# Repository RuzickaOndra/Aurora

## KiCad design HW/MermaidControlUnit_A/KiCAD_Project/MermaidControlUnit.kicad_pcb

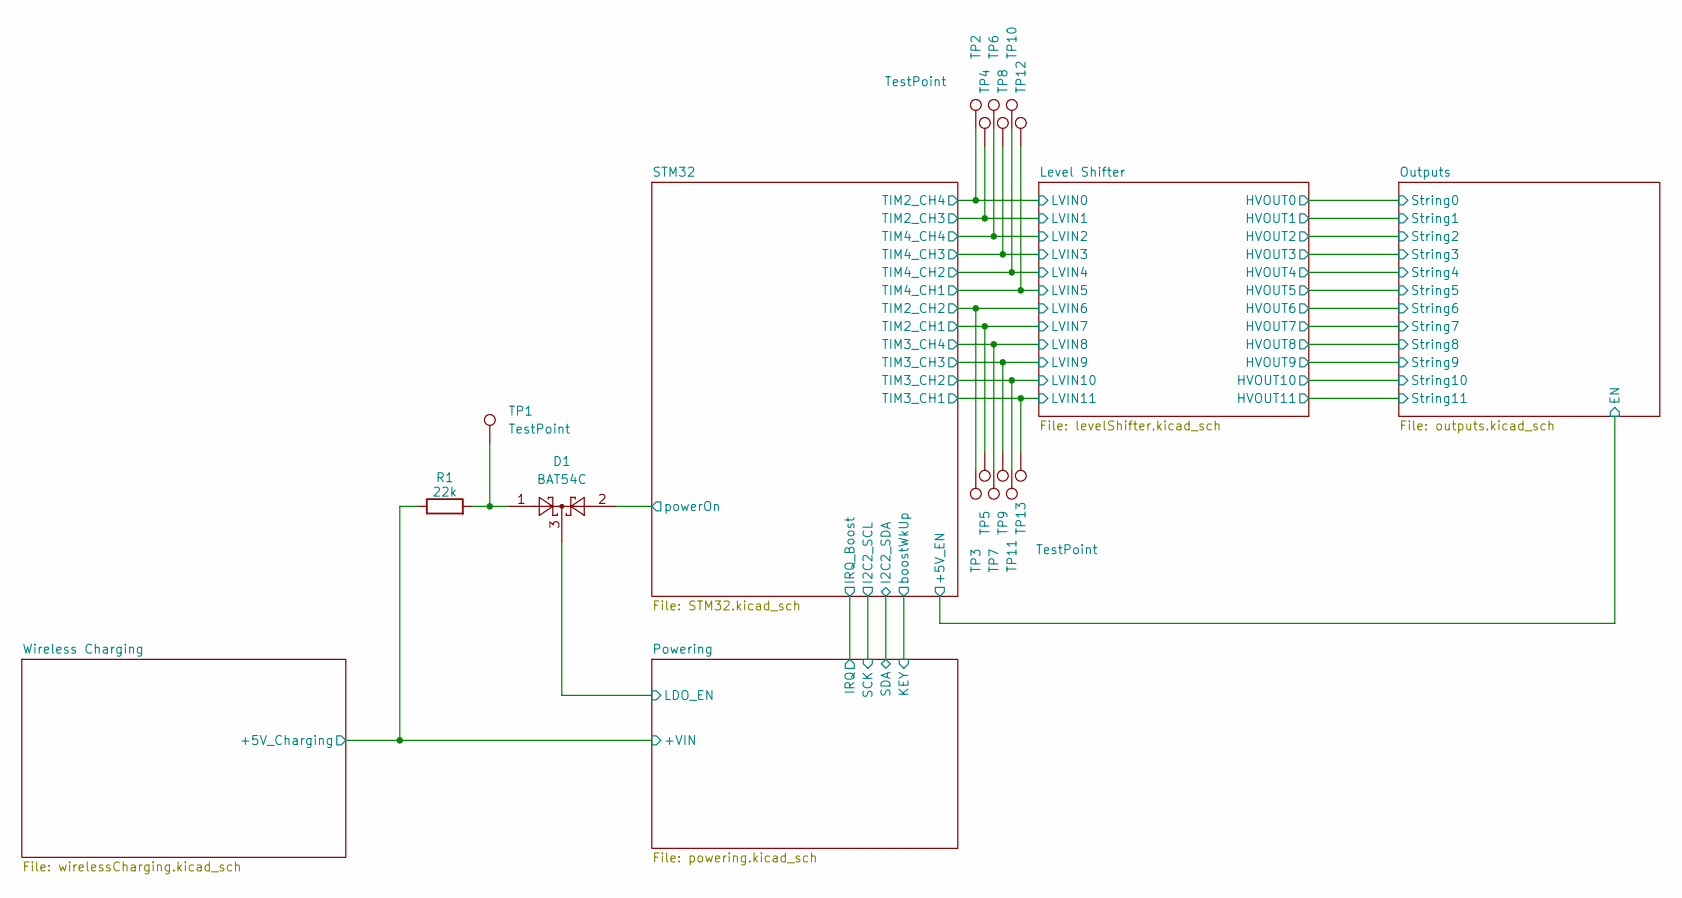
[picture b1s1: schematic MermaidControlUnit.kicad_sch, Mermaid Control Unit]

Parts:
D1: BAT54C; SOT-23; Part Number BAT54CLT1G
R1: 22k; R_0603_1608Metric; Part Number RC0603FR-0722KL
TP1, TP2, TP3, TP4, TP5, TP6, TP7, TP8, TP9, TP10, TP11, TP12, TP13: TestPoint; TestPoint_Pad_D1.5mm

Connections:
/Powering/LDO_EN: D1.3; also elsewhere on the board
/STM32/TIM2_CH1: TP5.1; also elsewhere on the board
/STM32/TIM2_CH2: TP3.1; also elsewhere on the board
/STM32/TIM2_CH3: TP4.1; also elsewhere on the board
/STM32/TIM2_CH4: TP2.1; also elsewhere on the board
/STM32/TIM3_CH1: TP13.1; also elsewhere on the board
/STM32/TIM3_CH2: TP11.1; also elsewhere on the board
/STM32/TIM3_CH3: TP9.1; also elsewhere on the board
/STM32/TIM3_CH4: TP7.1; also elsewhere on the board
/STM32/TIM4_CH1: TP12.1; also elsewhere on the board
/STM32/TIM4_CH2: TP10.1; also elsewhere on the board
/STM32/TIM4_CH3: TP8.1; also elsewhere on the board
/STM32/TIM4_CH4: TP6.1; also elsewhere on the board
/STM32/powerOn: D1.2; also elsewhere on the board
/Wireless Charging/+5V_Charging: R1.1; also elsewhere on the board
unnamed: D1.1, R1.2, TP1.1

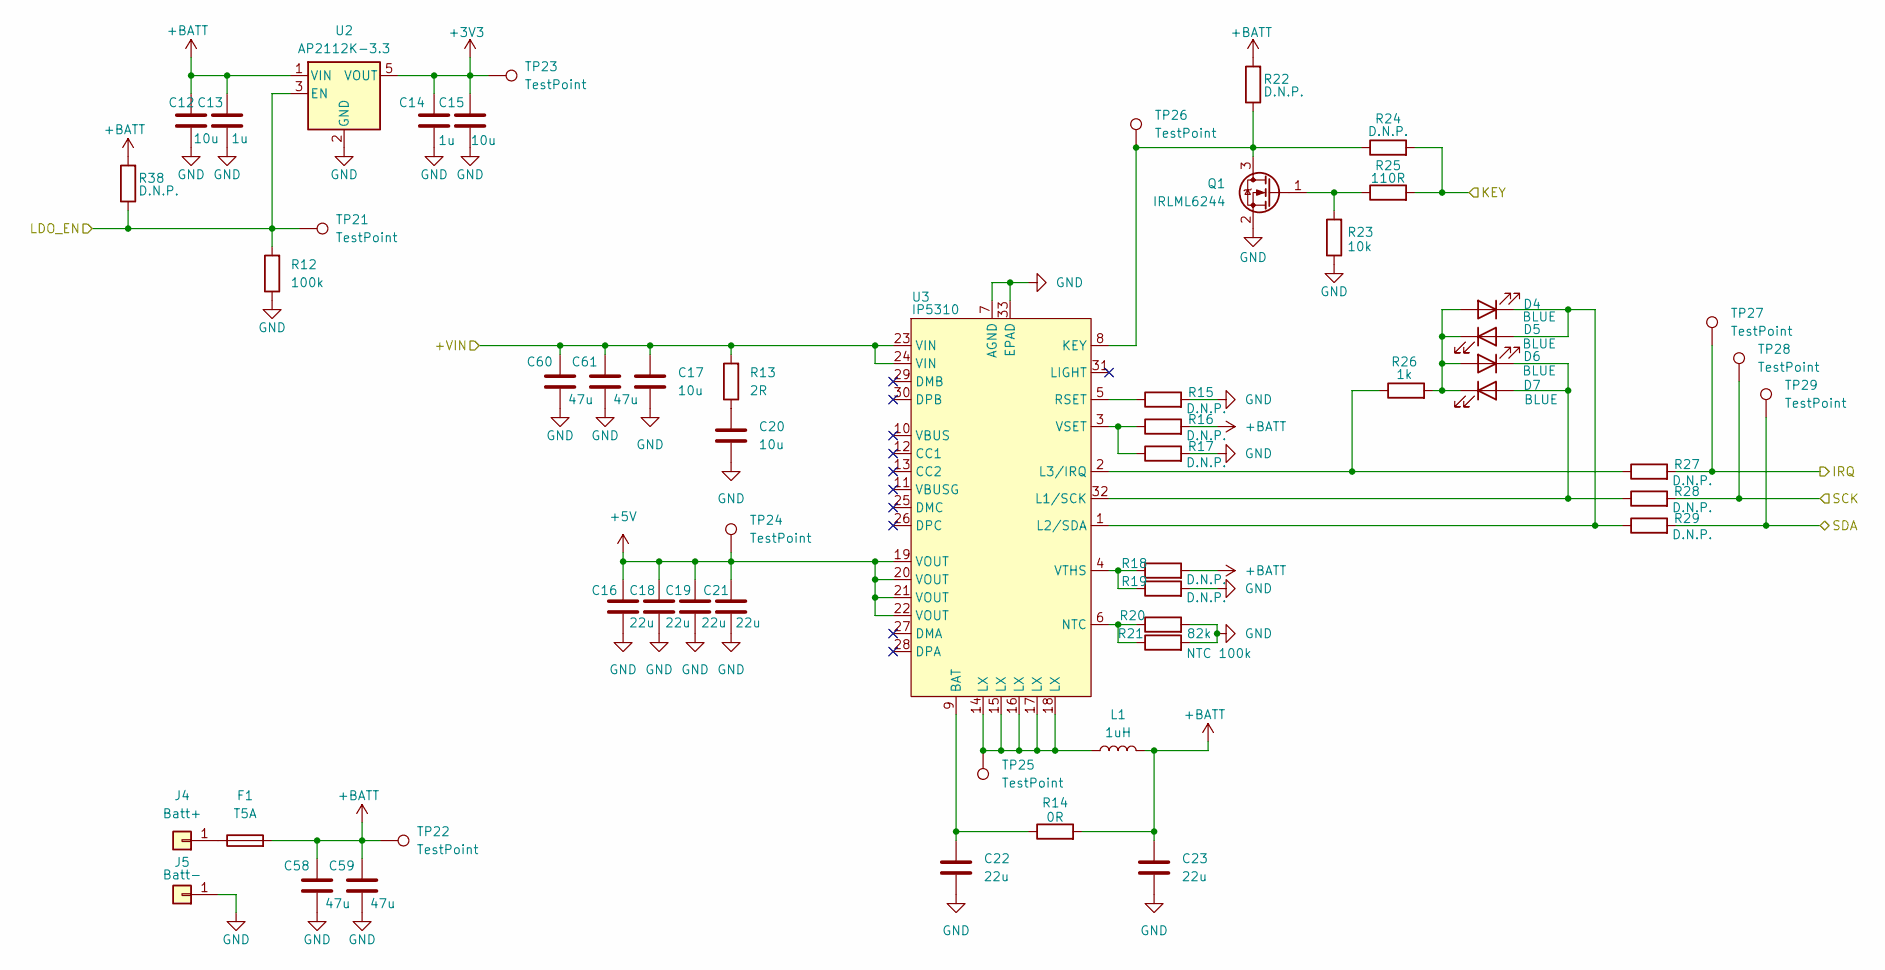
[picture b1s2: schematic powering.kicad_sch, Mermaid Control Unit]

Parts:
C12, C15, C17, C20: 10u; C_0603_1608Metric; Part Number CL10A106MA8NRNC
C13, C14: 1u; C_0603_1608Metric; Part Number CL10A105KB8NNNC
C16, C18, C19, C21, C22, C23: 22u; C_0603_1608Metric; Part Number CL10A226MP8NUNE
C58, C59, C60, C61: 47u; C_0805_2012Metric; Part Number GRM21BR61A476ME15L
D4, D5, D6, D7: BLUE; LED_0603_1608Metric; Part Number APT1608QBC/D
F1: T5A; Fuse_0603_1608Metric; Part Number F0603HI8000V032TM
J4: Batt+; TestPoint_THTPad_2.0x2.0mm_Drill1.0mm
J5: Batt-; TestPoint_THTPad_2.0x2.0mm_Drill1.0mm
L1: 1uH; L_PCC-M1040M-LP; Part Number ETQP4M1R0KVC
Q1: IRLML6244; SOT-23; Part Number IRLML6244TRPBF
R12: 100k; R_0603_1608Metric; Part Number RC0603FR-07100KL
R13: 2R; R_0603_1608Metric; Part Number FRC0603F2R00TS
R14: 0R; R_0603_1608Metric; Part Number RC0603FR-070RL
R15, R16, R17, R18, R19, R22, R24, R27, R28, R29, R38: D.N.P.; R_0603_1608Metric
R20: 82k; R_0603_1608Metric; Part Number RC0603FR-0782KL
R21: NTC 100k; R_0603_1608Metric; Part Number NCU18WF104F6SRB
R23: 10k; R_0603_1608Metric; Part Number RC0603FR-0710KL
R25: 110R; R_0603_1608Metric; Part Number 0603WAF1100T5E
R26: 1k; R_0603_1608Metric; Part Number RC0603FR-071KL
TP21, TP22, TP23, TP24, TP25, TP26, TP27, TP28, TP29: TestPoint; TestPoint_Pad_D1.5mm
U2: AP2112K-3.3; SOT-23-5; Part Number AP2112K-3.3TRG1
U3: IP5310; QFN-32-1EP_5x5mm_P0.5mm_EP3.6x3.6mm_ThermalVias; Part Number IP5310

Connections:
+3V3: C14.1, C15.1, TP23.1, U2.5 (VOUT); also elsewhere on the board
+5V: C16.1, C18.1, C19.1, C21.1, TP24.1, U3.19 (VOUT), U3.20 (VOUT), U3.21 (VOUT), U3.22 (VOUT); also elsewhere on the board
+BATT: C12.1, C13.1, C23.1, C58.1, C59.1, F1.2, L1.2, R14.2, R16.2, R18.2, R22.2, R38.2, TP22.1, U2.1 (VIN); also elsewhere on the board
/Powering/LDO_EN: R12.2, R38.1, TP21.1, U2.3 (EN); also elsewhere on the board
/STM32/I2C2_SCL: R28.2, TP28.1; also elsewhere on the board
/STM32/I2C2_SDA: R29.2, TP29.1; also elsewhere on the board
/STM32/IRQ_Boost: R27.2, TP27.1; also elsewhere on the board
/STM32/boostWkUp: R24.2, R25.2; also elsewhere on the board
/Wireless Charging/+5V_Charging: C17.1, C60.1, C61.1, R13.2, U3.23 (VIN), U3.24 (VIN); also elsewhere on the board
GND: C12.2, C13.2, C14.2, C15.2, C16.2, C17.2, C18.2, C19.2, C20.2, C21.2, C22.2, C23.2, C58.2, C59.2, C60.2, C61.2, J5.1, Q1.2 (S), R12.1, R15.2, R17.2, R19.2, R20.2, R21.2, R23.1, U2.2 (GND), U3.7 (AGND), U3.33 (EPAD); also elsewhere on the board
unnamed: C20.1, R13.1
unnamed: D4.2 (A), D5.1 (K), D6.2 (A), D7.1 (K), R26.2
unnamed: D4.1 (K), D5.2 (A), R29.1, U3.1 (L2/SDA)
unnamed: D6.1 (K), D7.2 (A), R28.1, U3.32 (L1/SCK)
unnamed: F1.1, J4.1
unnamed: L1.1, TP25.1, U3.14 (LX), U3.15 (LX), U3.16 (LX), U3.17 (LX), U3.18 (LX)
unnamed: Q1.3 (D), R22.1, R24.1, TP26.1, U3.8 (KEY)
unnamed: Q1.1 (G), R23.2, R25.1
unnamed: C22.1, R14.1, U3.9 (BAT)
unnamed: R26.1, R27.1, U3.2 (L3/IRQ)
unnamed: R20.1, R21.1, U3.6 (NTC)
unnamed: R15.1, U3.5 (RSET)
unnamed: R16.1, R17.1, U3.3 (VSET)
unnamed: R18.1, R19.1, U3.4 (VTHS)

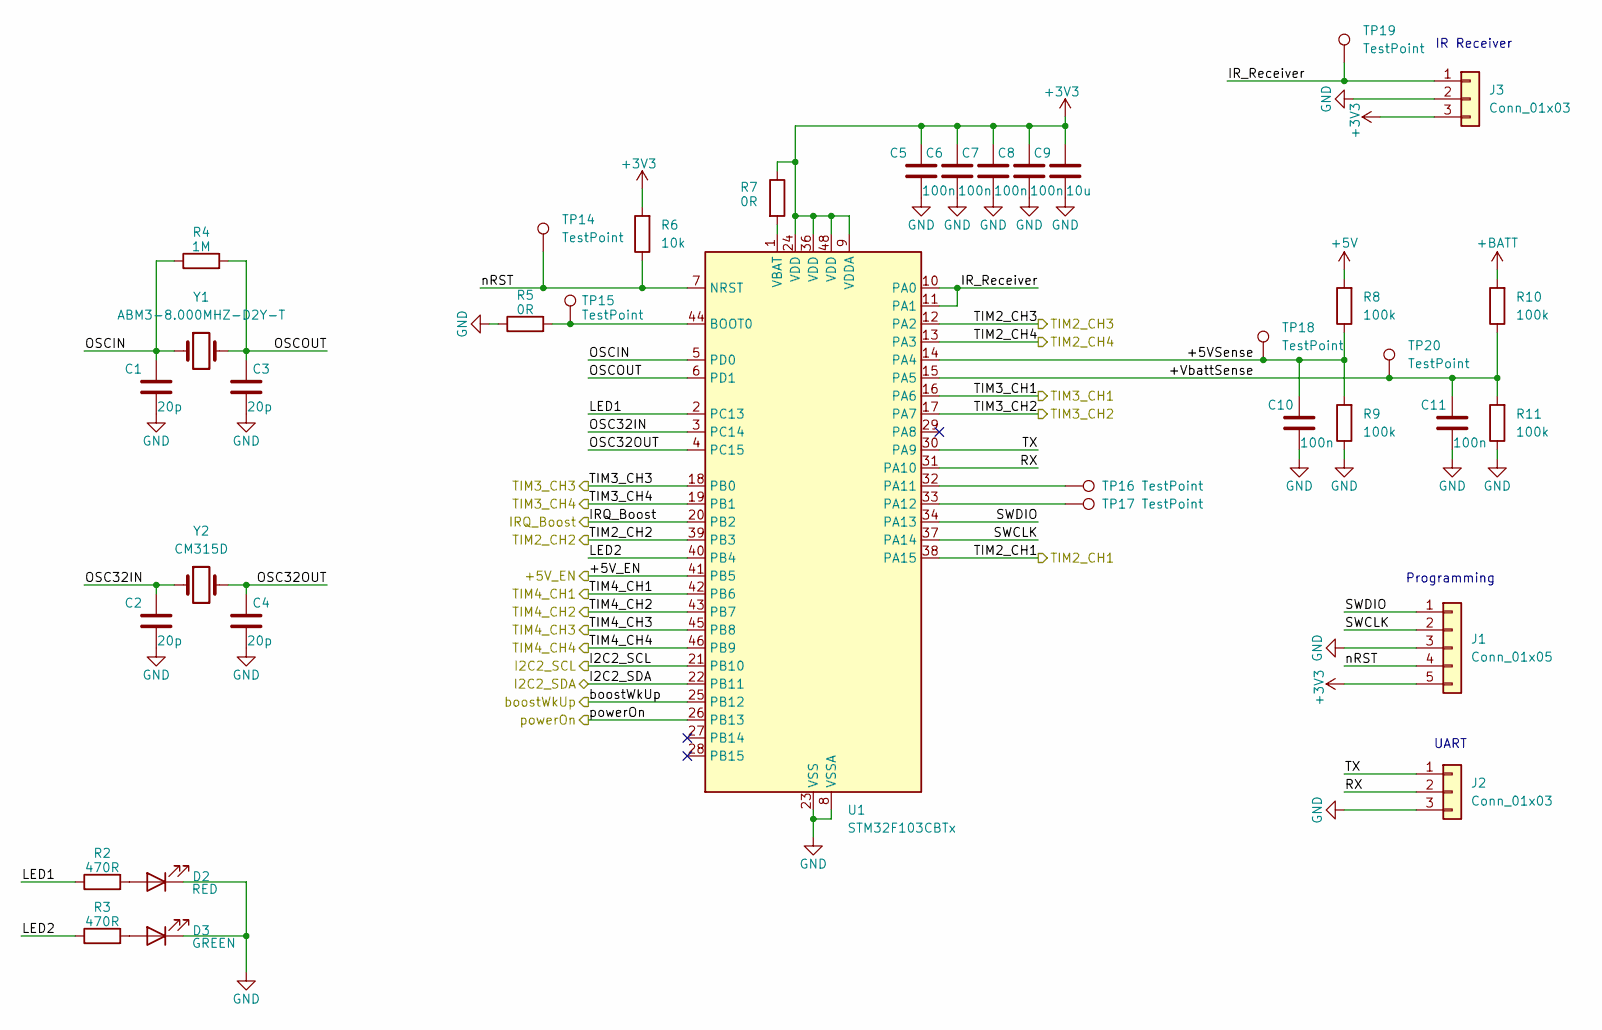
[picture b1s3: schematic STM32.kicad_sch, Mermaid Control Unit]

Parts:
C1, C2, C3, C4: 20p; C_0603_1608Metric; Part Number GCM1885C1H200JA16D
C5, C6, C7, C8, C10, C11: 100n; C_0603_1608Metric; Part Number CC0603KRX7R9BB104
C9: 10u; C_0603_1608Metric; Part Number CL10A106MA8NRNC
D2: RED; LED_0603_1608Metric; Part Number APT1608EC
D3: GREEN; LED_0603_1608Metric; Part Number APT1608CGCK
J1: Conn_01x05; PinHeader_1x05_P2.54mm_Horizontal_SmallSilk; Part Number 5AMW4-10560-105-W0
J2, J3: Conn_01x03; PinHeader_1x03_P2.54mm_Horizontal_SmallSilk; Part Number X6511WR-03H-C60D30R2
R2, R3: 470R; R_0603_1608Metric; Part Number RC0603FR-07470RL
R4: 1M; R_0603_1608Metric; Part Number RC0603FR-071ML
R5, R7: 0R; R_0603_1608Metric; Part Number RC0603FR-070RL
R6: 10k; R_0603_1608Metric; Part Number RC0603FR-0710KL
R8, R9, R10, R11: 100k; R_0603_1608Metric; Part Number RC0603FR-07100KL
TP14, TP15, TP16, TP17, TP18, TP19, TP20: TestPoint; TestPoint_Pad_D1.5mm
U1: STM32F103CBTx; LQFP-48_7x7mm_P0.5mm
Y1: ABM3-8.000MHZ-D2Y-T; Crystal_SMD_Abracon_ABM3-2Pin_5.0x3.2mm; Part Number ABM3-8.000MHZ-D2Y-T
Y2: CM315D; Crystal_SMD_3215-2Pin_3.2x1.5mm; Part Number CM315D32768DZFT

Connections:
+3V3: C5.1, C6.1, C7.1, C8.1, C9.1, J1.5, J3.3, R6.2, R7.1, U1.9 (VDDA), U1.24 (VDD), U1.36 (VDD), U1.48 (VDD); also elsewhere on the board
+5V: R8.2; also elsewhere on the board
+BATT: R10.2; also elsewhere on the board
/STM32/+5VSense: C10.1, R8.1, R9.2, TP18.1, U1.14 (PA4)
/STM32/+5V_EN: U1.41 (PB5); also elsewhere on the board
/STM32/+VbattSense: C11.1, R10.1, R11.2, TP20.1, U1.15 (PA5)
/STM32/I2C2_SCL: U1.21 (PB10); also elsewhere on the board
/STM32/I2C2_SDA: U1.22 (PB11); also elsewhere on the board
/STM32/IRQ_Boost: U1.20 (PB2); also elsewhere on the board
/STM32/IR_Receiver: J3.1, TP19.1, U1.10 (PA0), U1.11 (PA1)
/STM32/LED1: R2.1, U1.2 (PC13)
/STM32/LED2: R3.1, U1.40 (PB4)
/STM32/OSC32IN: C2.1, U1.3 (PC14), Y2.1
/STM32/OSC32OUT: C4.1, U1.4 (PC15), Y2.2
/STM32/OSCIN: C1.1, R4.1, U1.5 (PD0), Y1.1
/STM32/OSCOUT: C3.1, R4.2, U1.6 (PD1), Y1.2
/STM32/RX: J2.2, U1.31 (PA10)
/STM32/SWCLK: J1.2, U1.37 (PA14)
/STM32/SWDIO: J1.1, U1.34 (PA13)
/STM32/TIM2_CH1: U1.38 (PA15); also elsewhere on the board
/STM32/TIM2_CH2: U1.39 (PB3); also elsewhere on the board
/STM32/TIM2_CH3: U1.12 (PA2); also elsewhere on the board
/STM32/TIM2_CH4: U1.13 (PA3); also elsewhere on the board
/STM32/TIM3_CH1: U1.16 (PA6); also elsewhere on the board
/STM32/TIM3_CH2: U1.17 (PA7); also elsewhere on the board
/STM32/TIM3_CH3: U1.18 (PB0); also elsewhere on the board
/STM32/TIM3_CH4: U1.19 (PB1); also elsewhere on the board
/STM32/TIM4_CH1: U1.42 (PB6); also elsewhere on the board
/STM32/TIM4_CH2: U1.43 (PB7); also elsewhere on the board
/STM32/TIM4_CH3: U1.45 (PB8); also elsewhere on the board
/STM32/TIM4_CH4: U1.46 (PB9); also elsewhere on the board
/STM32/TX: J2.1, U1.30 (PA9)
/STM32/boostWkUp: U1.25 (PB12); also elsewhere on the board
/STM32/nRST: J1.4, R6.1, TP14.1, U1.7 (NRST)
/STM32/powerOn: U1.26 (PB13); also elsewhere on the board
GND: C1.2, C2.2, C3.2, C4.2, C5.2, C6.2, C7.2, C8.2, C9.2, C10.2, C11.2, D2.1 (K), D3.1 (K), J1.3, J2.3, J3.2, R5.1, R9.1, R11.1, U1.8 (VSSA), U1.23 (VSS), U1.35 (VSS), U1.47 (VSS); also elsewhere on the board
unnamed: D2.2 (A), R2.2
unnamed: D3.2 (A), R3.2
unnamed: R5.2, TP15.1, U1.44 (BOOT0)
unnamed: TP16.1, U1.32 (PA11)
unnamed: TP17.1, U1.33 (PA12)
unnamed: R7.2, U1.1 (VBAT)

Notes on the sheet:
Programming
UART
IR Receiver

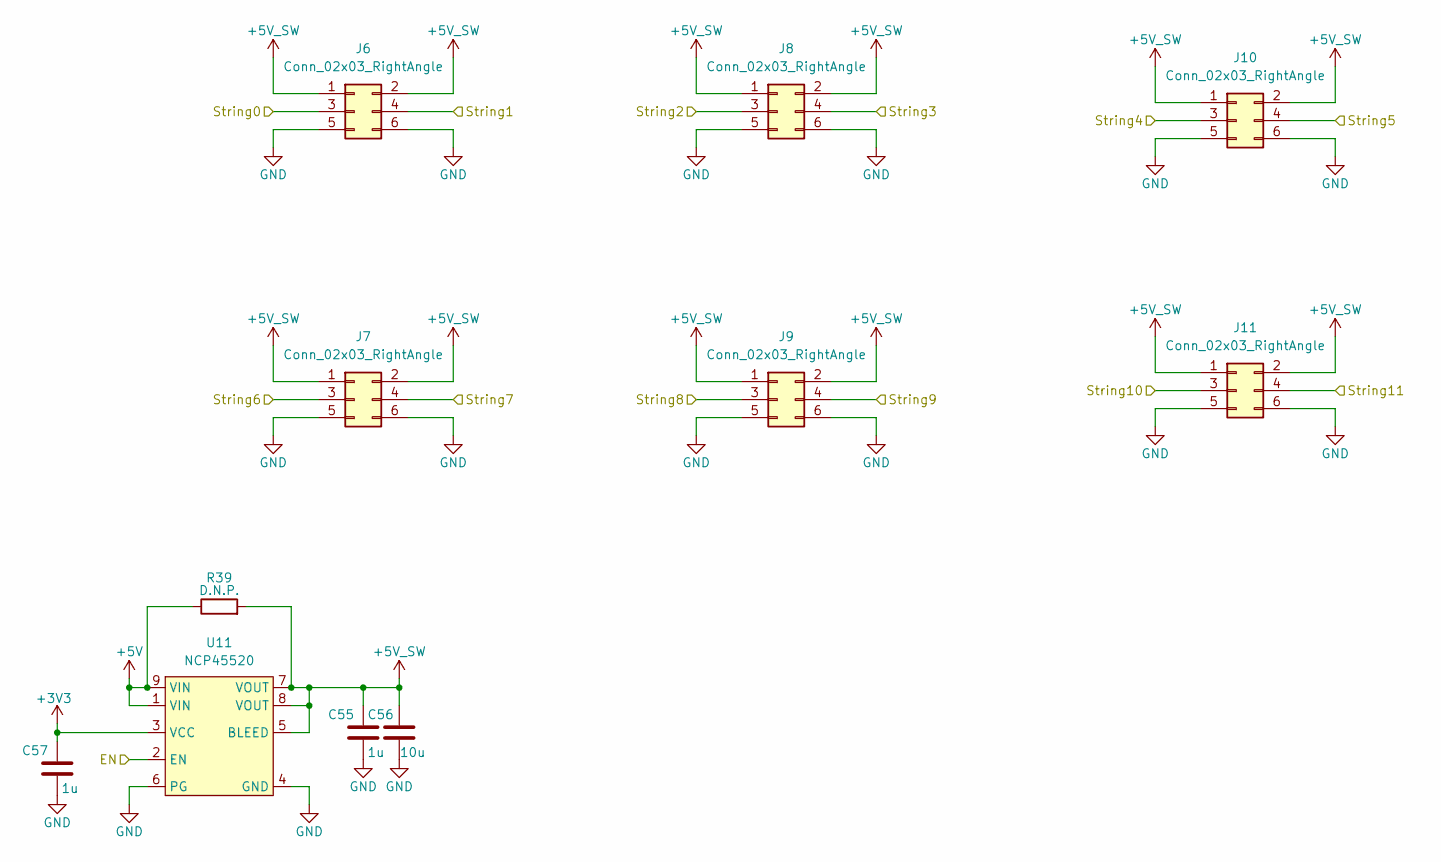
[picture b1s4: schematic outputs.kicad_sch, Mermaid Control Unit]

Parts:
C55, C57: 1u; C_0603_1608Metric; Part Number CL10A105KB8NNNC
C56: 10u; C_0603_1608Metric; Part Number CL10A106MA8NRNC
J6, J7, J8, J9, J10, J11: Conn_02x03_RightAngle; PinHeader_2x03_P2.54mm_Horizontal_SmallSilk; Part Number BX-PZ2.54-2-3PWZ
R39: D.N.P.; R_0603_1608Metric
U11: NCP45520; DFN-8-1EP_2x2mm_P0.5mm_EP1.05x1.75mm; Part Number NCP45520IMNTWG-H

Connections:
+3V3: C57.1, U11.3 (VCC); also elsewhere on the board
+5V: R39.1, U11.1 (VIN), U11.9 (VIN); also elsewhere on the board
+5V_SW: C55.1, C56.1, J6.1, J6.2, J7.1, J7.2, J8.1, J8.2, J9.1, J9.2, J10.1, J10.2, J11.1, J11.2, R39.2, U11.5 (BLEED), U11.7 (VOUT), U11.8 (VOUT)
/Level Shifter/HVOUT0: J6.3; also elsewhere on the board
/Level Shifter/HVOUT1: J6.4; also elsewhere on the board
/Level Shifter/HVOUT2: J8.3; also elsewhere on the board
/Level Shifter/HVOUT3: J8.4; also elsewhere on the board
/Level Shifter/HVOUT4: J10.3; also elsewhere on the board
/Level Shifter/HVOUT5: J10.4; also elsewhere on the board
/Level Shifter/HVOUT6: J7.3; also elsewhere on the board
/Level Shifter/HVOUT7: J7.4; also elsewhere on the board
/Level Shifter/HVOUT8: J9.3; also elsewhere on the board
/Level Shifter/HVOUT9: J9.4; also elsewhere on the board
/Level Shifter/HVOUT10: J11.3; also elsewhere on the board
/Level Shifter/HVOUT11: J11.4; also elsewhere on the board
/STM32/+5V_EN: U11.2 (EN); also elsewhere on the board
GND: C55.2, C56.2, C57.2, J6.5, J6.6, J7.5, J7.6, J8.5, J8.6, J9.5, J9.6, J10.5, J10.6, J11.5, J11.6, U11.4 (GND), U11.6 (PG); also elsewhere on the board

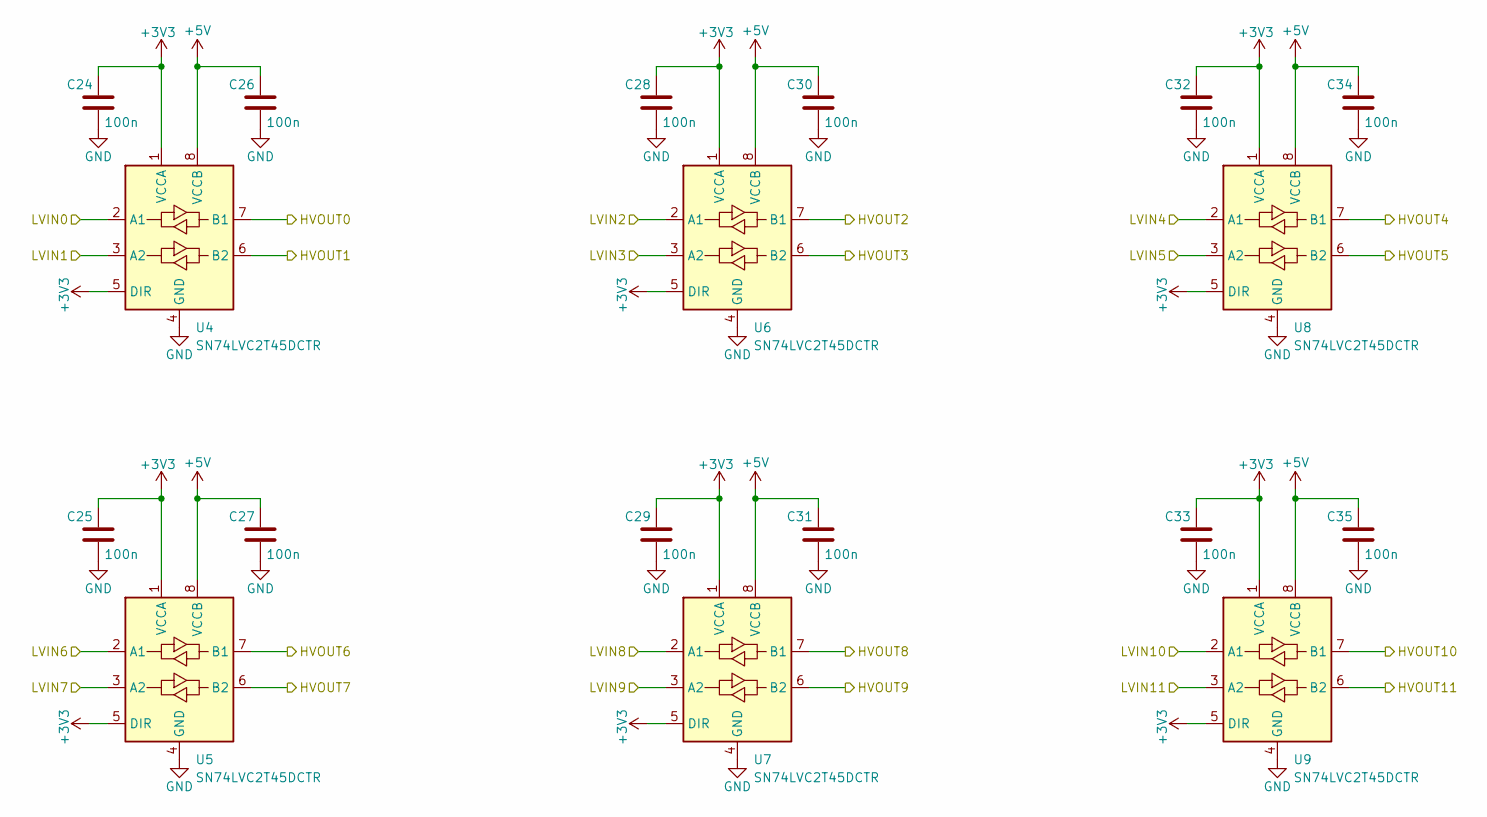
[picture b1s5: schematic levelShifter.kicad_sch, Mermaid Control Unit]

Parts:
C24, C25, C26, C27, C28, C29, C30, C31, C32, C33, C34, C35: 100n; C_0603_1608Metric; Part Number CC0603KRX7R9BB104
U4, U5, U6, U7, U8, U9: SN74LVC2T45DCTR; SSOP-8_2.95x2.8mm_P0.65mm; Part Number SN74LVC2T45DCTR

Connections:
+3V3: C24.1, C25.1, C28.1, C29.1, C32.1, C33.1, U4.1 (VCCA), U4.5 (DIR), U5.1 (VCCA), U5.5 (DIR), U6.1 (VCCA), U6.5 (DIR), U7.1 (VCCA), U7.5 (DIR), U8.1 (VCCA), U8.5 (DIR), U9.1 (VCCA), U9.5 (DIR); also elsewhere on the board
+5V: C26.1, C27.1, C30.1, C31.1, C34.1, C35.1, U4.8 (VCCB), U5.8 (VCCB), U6.8 (VCCB), U7.8 (VCCB), U8.8 (VCCB), U9.8 (VCCB); also elsewhere on the board
/Level Shifter/HVOUT0: U4.7 (B1); also elsewhere on the board
/Level Shifter/HVOUT1: U4.6 (B2); also elsewhere on the board
/Level Shifter/HVOUT2: U6.7 (B1); also elsewhere on the board
/Level Shifter/HVOUT3: U6.6 (B2); also elsewhere on the board
/Level Shifter/HVOUT4: U8.7 (B1); also elsewhere on the board
/Level Shifter/HVOUT5: U8.6 (B2); also elsewhere on the board
/Level Shifter/HVOUT6: U5.7 (B1); also elsewhere on the board
/Level Shifter/HVOUT7: U5.6 (B2); also elsewhere on the board
/Level Shifter/HVOUT8: U7.7 (B1); also elsewhere on the board
/Level Shifter/HVOUT9: U7.6 (B2); also elsewhere on the board
/Level Shifter/HVOUT10: U9.7 (B1); also elsewhere on the board
/Level Shifter/HVOUT11: U9.6 (B2); also elsewhere on the board
/STM32/TIM2_CH1: U5.3 (A2); also elsewhere on the board
/STM32/TIM2_CH2: U5.2 (A1); also elsewhere on the board
/STM32/TIM2_CH3: U4.3 (A2); also elsewhere on the board
/STM32/TIM2_CH4: U4.2 (A1); also elsewhere on the board
/STM32/TIM3_CH1: U9.3 (A2); also elsewhere on the board
/STM32/TIM3_CH2: U9.2 (A1); also elsewhere on the board
/STM32/TIM3_CH3: U7.3 (A2); also elsewhere on the board
/STM32/TIM3_CH4: U7.2 (A1); also elsewhere on the board
/STM32/TIM4_CH1: U8.3 (A2); also elsewhere on the board
/STM32/TIM4_CH2: U8.2 (A1); also elsewhere on the board
/STM32/TIM4_CH3: U6.3 (A2); also elsewhere on the board
/STM32/TIM4_CH4: U6.2 (A1); also elsewhere on the board
GND: C24.2, C25.2, C26.2, C27.2, C28.2, C29.2, C30.2, C31.2, C32.2, C33.2, C34.2, C35.2, U4.4 (GND), U5.4 (GND), U6.4 (GND), U7.4 (GND), U8.4 (GND), U9.4 (GND); also elsewhere on the board

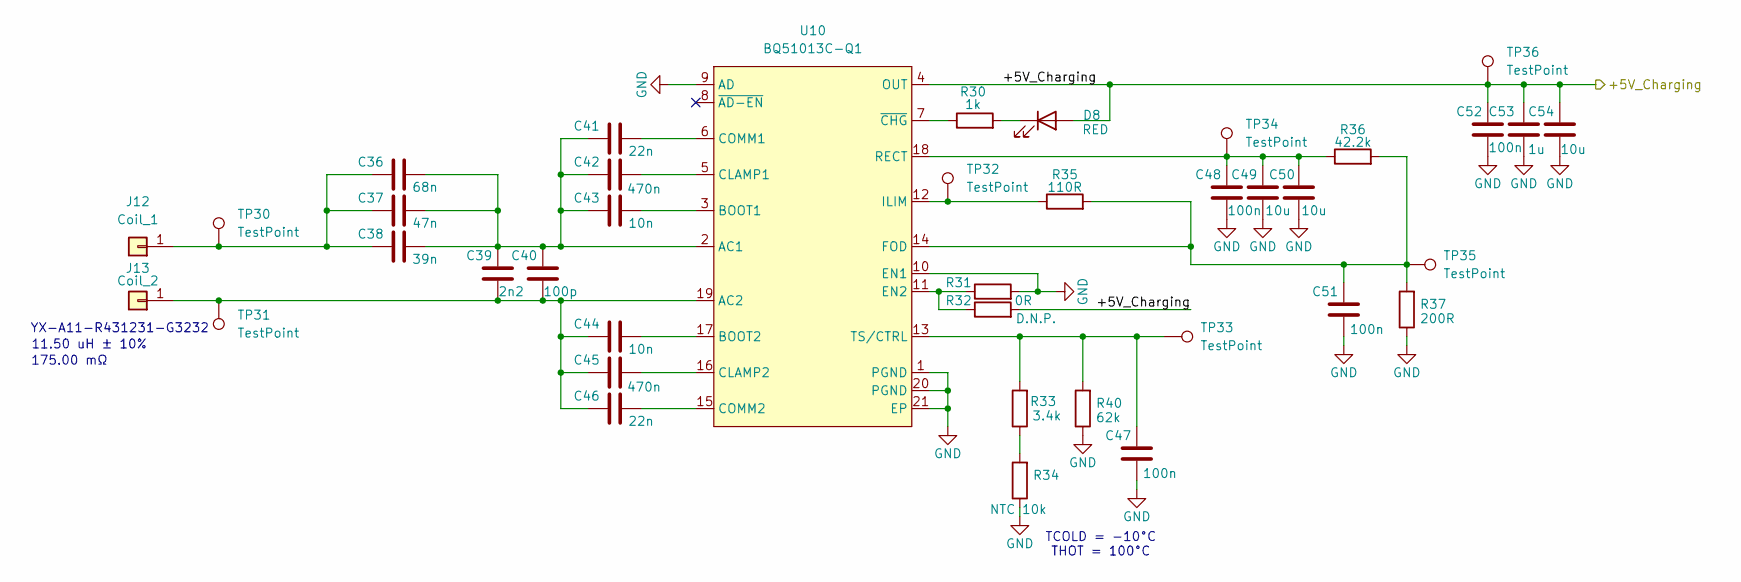
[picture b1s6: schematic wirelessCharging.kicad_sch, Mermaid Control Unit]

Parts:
C36: 68n; C_0603_1608Metric; Part Number GCJ188R71H683KA12D
C37: 47n; C_0603_1608Metric; Part Number CGA3E2X7R1H473KT0Y0N
C38: 39n; C_0603_1608Metric; Part Number CL10B393KB8NNNC
C39: 2n2; C_0603_1608Metric; Part Number GRM1885C2A222JA01D
C40: 100p; C_0603_1608Metric; Part Number CGA3E2C0G1H101JT0Y0N
C41, C46: 22n; C_0603_1608Metric; Part Number C1608X7R1H223KT000N
C42, C45: 470n; C_0603_1608Metric; Part Number CL10B474KB8VPNC
C43, C44: 10n; C_0603_1608Metric; Part Number 06035C103JAT2A
C47, C48, C51, C52: 100n; C_0603_1608Metric; Part Number CC0603KRX7R9BB104
C49, C50, C54: 10u; C_0603_1608Metric; Part Number CL10A106MA8NRNC
C53: 1u; C_0603_1608Metric; Part Number CL10A105KB8NNNC
D8: RED; LED_0603_1608Metric; Part Number APT1608EC
J12: Coil_1; TestPoint_THTPad_2.0x2.0mm_Drill1.0mm
J13: Coil_2; TestPoint_THTPad_2.0x2.0mm_Drill1.0mm
R30: 1k; R_0603_1608Metric; Part Number RC0603FR-071KL
R31: 0R; R_0603_1608Metric; Part Number RC0603FR-070RL
R32: D.N.P.; R_0603_1608Metric
R33: 3.4k; R_0603_1608Metric; Part Number 0603WAF4301T5E
R34: NTC 10k; R_0603_1608Metric; Part Number NTCG163JF103FTDS
R35: 110R; R_0603_1608Metric; Part Number 0603WAF1100T5E
R36: 42.2k; R_0603_1608Metric; Part Number WR06X4222FTL
R37: 200R; R_0603_1608Metric; Part Number 0603WAF2000T5E
R40: 62k; R_0603_1608Metric; Part Number 0603WAF6202T5E
TP30, TP31, TP32, TP33, TP34, TP35, TP36: TestPoint; TestPoint_Pad_D1.5mm
U10: BQ51013C-Q1; Texas_VQFN-RHL-20_ThermalVias; Part Number BQ51013C-Q1

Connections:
/Wireless Charging/+5V_Charging: C52.1, C53.1, C54.1, D8.2 (A), R32.2, TP36.1, U10.4 (OUT); also elsewhere on the board
GND: C47.2, C48.2, C49.2, C50.2, C51.2, C52.2, C53.2, C54.2, R31.2, R34.1, R37.1, R40.1, U10.1 (PGND), U10.9 (AD), U10.10 (EN1), U10.20 (PGND), U10.21 (EP); also elsewhere on the board
unnamed: D8.1 (K), R30.2
unnamed: C36.1, C37.1, C38.1, J12.1, TP30.1
unnamed: C39.2, C40.2, C44.1, C45.1, C46.1, J13.1, TP31.1, U10.19 (AC2)
unnamed: R33.1, R34.2
unnamed: C36.2, C37.2, C38.2, C39.1, C40.1, C41.1, C42.1, C43.1, U10.2 (AC1)
unnamed: C43.2, U10.3 (BOOT1)
unnamed: C44.2, U10.17 (BOOT2)
unnamed: C42.2, U10.5 (CLAMP1)
unnamed: C45.2, U10.16 (CLAMP2)
unnamed: C41.2, U10.6 (COMM1)
unnamed: C46.2, U10.15 (COMM2)
unnamed: R31.1, R32.1, U10.11 (EN2)
unnamed: C51.1, R35.2, R36.2, R37.2, TP35.1, U10.14 (FOD)
unnamed: R35.1, TP32.1, U10.12 (ILIM)
unnamed: C48.1, C49.1, C50.1, R36.1, TP34.1, U10.18 (RECT)
unnamed: C47.1, R33.2, R40.2, TP33.1, U10.13 (TS/CTRL)
unnamed: R30.1, U10.7 (~CHG)

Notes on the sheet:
175.00 mΩ
11.50 uH ± 10%
YX-A11-R431231-G3232
TCOLD = -10°C THOT = 100°C

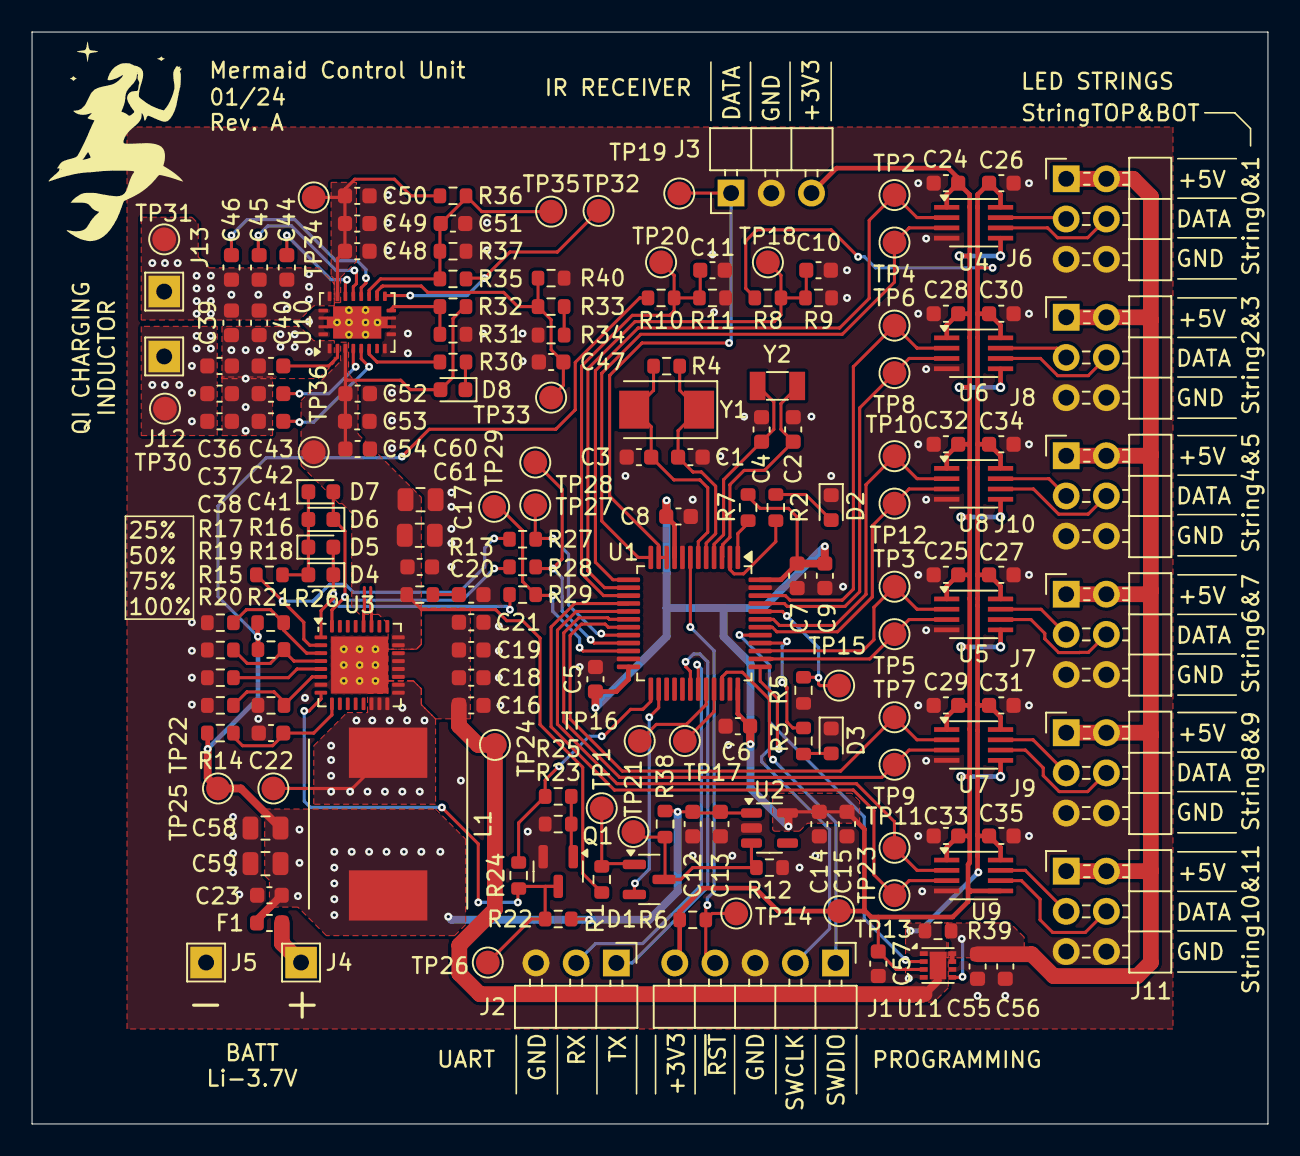
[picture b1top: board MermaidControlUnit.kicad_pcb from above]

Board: 2 copper layers, 78.1 x 69.0 mm, 174 parts (0 on the bottom side), 89 nets.

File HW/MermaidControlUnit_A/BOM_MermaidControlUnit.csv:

"Reference","Value","Datasheet","Footprint","Qty","DNP","Part Number"
"C1,C2,C3,C4","20p","~","Capacitor_SMD:C_0603_1608Metric","4","","GCM1885C1H200JA16D"
"C5,C6,C7,C8,C10,C11,C24,C25,C26,C27,C28,C29,C30,C31,C32,C33,C34,C35,C47,C48,C51,C52","100n","~","Capacitor_SMD:C_0603_1608Metric","22","","CC0603KRX7R9BB104"
"C9,C12,C15,C17,C20,C49,C50,C54,C56","10u","~","Capacitor_SMD:C_0603_1608Metric","9","","CL10A106MA8NRNC "
"C13,C14,C53,C55,C57","1u","~","Capacitor_SMD:C_0603_1608Metric","5","","CL10A105KB8NNNC "
"C16,C18,C19,C21,C22,C23","22u","~","Capacitor_SMD:C_0603_1608Metric","6","","CL10A226MP8NUNE "
"C36","68n","~","Capacitor_SMD:C_0603_1608Metric","1","","GCJ188R71H683KA12D"
"C37","47n","~","Capacitor_SMD:C_0603_1608Metric","1","","CGA3E2X7R1H473KT0Y0N "
"C38","39n","~","Capacitor_SMD:C_0603_1608Metric","1","","CL10B393KB8NNNC "
"C39","2n2","~","Capacitor_SMD:C_0603_1608Metric","1","","GRM1885C2A222JA01D "
"C40","100p","~","Capacitor_SMD:C_0603_1608Metric","1","","CGA3E2C0G1H101JT0Y0N "
"C41,C46","22n","~","Capacitor_SMD:C_0603_1608Metric","2","","C1608X7R1H223KT000N "
"C42,C45","470n","~","Capacitor_SMD:C_0603_1608Metric","2","","CL10B474KB8VPNC "
"C43,C44","10n","~","Capacitor_SMD:C_0603_1608Metric","2","","06035C103JAT2A "
"C58,C59,C60,C61","47u","~","Capacitor_SMD:C_0805_2012Metric","4","","GRM21BR61A476ME15L "
"D1","BAT54C","http://www.diodes.com/_files/datasheets/ds11005.pdf","Package_TO_SOT_SMD:SOT-23","1","","BAT54CLT1G"
"D2,D8","RED","~","LED_SMD:LED_0603_1608Metric","2","","APT1608EC"
"D3","GREEN","~","LED_SMD:LED_0603_1608Metric","1","","APT1608CGCK"
"D4,D5,D6,D7","BLUE","~","LED_SMD:LED_0603_1608Metric","4","","APT1608QBC/D"
"F1","T5A","~","Fuse:Fuse_0603_1608Metric","1","","F0603HI8000V032TM"
"J1","Conn_01x05","~","Library:PinHeader_1x05_P2.54mm_Horizontal_SmallSilk","1","","5AMW4-10560-105-W0"
"J2,J3","Conn_01x03","~","Library:PinHeader_1x03_P2.54mm_Horizontal_SmallSilk","2","","X6511WR-03H-C60D30R2"
"J4","Batt+","~","TestPoint:TestPoint_THTPad_2.0x2.0mm_Drill1.0mm","1","",""
"J5","Batt-","~","TestPoint:TestPoint_THTPad_2.0x2.0mm_Drill1.0mm","1","",""
"J6,J7,J8,J9,J10,J11","Conn_02x03_RightAngle","~","Library:PinHeader_2x03_P2.54mm_Horizontal_SmallSilk","6","","BX-PZ2.54-2-3PWZ"
"J12","Coil_1","~","TestPoint:TestPoint_THTPad_2.0x2.0mm_Drill1.0mm","1","",""
"J13","Coil_2","~","TestPoint:TestPoint_THTPad_2.0x2.0mm_Drill1.0mm","1","",""
"L1","1uH","~","Inductor_SMD:L_PCC-M1040M-LP","1","","ETQP4M1R0KVC"
"Q1","IRLML6244","https://www.infineon.com/dgdl/Infineon-IRLML6244-DataSheet-v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","Package_TO_SOT_SMD:SOT-23","1","","IRLML6244TRPBF "
"R1","22k","~","Resistor_SMD:R_0603_1608Metric","1","","RC0603FR-0722KL"
"R2,R3","470R","~","Resistor_SMD:R_0603_1608Metric","2","","RC0603FR-07470RL "
"R4","1M","~","Resistor_SMD:R_0603_1608Metric","1","","RC0603FR-071ML "
"R5,R7,R14,R31","0R","~","Resistor_SMD:R_0603_1608Metric","4","","RC0603FR-070RL "
"R6,R23","10k","~","Resistor_SMD:R_0603_1608Metric","2","","RC0603FR-0710KL "
"R8,R9,R10,R11,R12","100k","~","Resistor_SMD:R_0603_1608Metric","5","","RC0603FR-07100KL "
"R13","2R","~","Resistor_SMD:R_0603_1608Metric","1","","FRC0603F2R00TS "
"R15,R16,R17,R18,R19,R22,R24,R27,R28,R29,R32,R38,R39","D.N.P.","~","Resistor_SMD:R_0603_1608Metric","13","",""
"R20","82k","~","Resistor_SMD:R_0603_1608Metric","1","","RC0603FR-0782KL "
"R21,R34","NTC 100k","~","Resistor_SMD:R_0603_1608Metric","2","","NCU18WF104F6SRB"
"R25,R33,R35","110R","~","Resistor_SMD:R_0603_1608Metric","3","","0603WAF1100T5E "
"R26,R30","1k","~","Resistor_SMD:R_0603_1608Metric","2","","RC0603FR-071KL "
"R36","42.2k","~","Resistor_SMD:R_0603_1608Metric","1","","WR06X4222FTL "
"R37","200R","~","Resistor_SMD:R_0603_1608Metric","1","","0603WAF2000T5E "
"R40","30k","~","Resistor_SMD:R_0603_1608Metric","1","","0603WAF3002T5E "
"TP1,TP2,TP3,TP4,TP5,TP6,TP7,TP8,TP9,TP10,TP11,TP12,TP13,TP14,TP15,TP16,TP17,TP18,TP19,TP20,TP21,TP22,TP23,TP24,TP25,TP26,TP27,TP28,TP29,TP30,TP31,TP32,TP33,TP34,TP35,TP36","TestPoint","~","TestPoint:TestPoint_Pad_D1.5mm","36","",""
"U1","STM32F103CBTx","https://www.st.com/resource/en/datasheet/stm32f103cb.pdf","Package_QFP:LQFP-48_7x7mm_P0.5mm","1","",""
"U2","AP2112K-3.3","https://www.diodes.com/assets/Datasheets/AP2112.pdf","Package_TO_SOT_SMD:SOT-23-5","1","","AP2112K-3.3TRG1 "
"U3","IP5310","http://www.injoinic.com/wwwroot/uploads/files/20200221/a7a61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","Package_DFN_QFN:QFN-32-1EP_5x5mm_P0.5mm_EP3.6x3.6mm_ThermalVias","1","","IP5310 "
"U4,U5,U6,U7,U8,U9","SN74LVC2T45DCTR","http://www.ti.com/lit/ds/symlink/sn74lvc2t45.pdf","Package_SO:SSOP-8_2.95x2.8mm_P0.65mm","6","","SN74LVC2T45DCTR"
"U10","BQ51013C-Q1","https://www.ti.com/lit/ds/symlink/bq51013c-q1.pdf?ts=1735290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","Package_DFN_QFN:Texas_VQFN-RHL-20_ThermalVias","1","","BQ51013C-Q1"
"U11","NCP45520","https://www.lcsc.com/datasheet/lcsc_datasheet_2109101130_ons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","Package_DFN_QFN:DFN-8-1EP_2x2mm_P0.5mm_EP1.05x1.75mm","1","","NCP45520IMNTWG-H "
"Y1","ABM3-8.000MHZ-D2Y-T","https://www.lcsc.com/datasheet/lcsc_datasheet_2304140030_Abr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","Crystal:Crystal_SMD_Abracon_ABM3-2Pin_5.0x3.2mm","1","","ABM3-8.000MHZ-D2Y-T"
"Y2","CM315D","https://www.lcsc.com/datasheet/lcsc_datasheet_1810161213_CIT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","Crystal:Crystal_SMD_3215-2Pin_3.2x1.5mm","1","","CM315D32768DZFT "

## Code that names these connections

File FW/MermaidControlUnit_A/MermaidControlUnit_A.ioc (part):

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Mcu.Name=STM32F103C(8-B)Tx
Mcu.Package=LQFP48
Mcu.UserName=STM32F103CBTx
PA1.GPIOParameters=GPIO_ModeDefaultEXTI
PA1.GPIO_ModeDefaultEXTI=GPIO_MODE_IT_FALLING
PA1.Signal=GPXTI1
PA10.Mode=Asynchronous
PA10.Signal=USART1_RX
PA13.Mode=Serial_Wire
PA13.Signal=SYS_JTMS-SWDIO
PA14.Mode=Serial_Wire
PA14.Signal=SYS_JTCK-SWCLK
PA15.Signal=S_TIM2_CH1_ETR
PA2.Signal=S_TIM2_CH3
PA3.Signal=S_TIM2_CH4
PA4.Signal=ADCx_IN4
PA5.Signal=ADCx_IN5
PA6.Signal=S_TIM3_CH1
PA7.Signal=S_TIM3_CH2
PA9.Mode=Asynchronous
PA9.Signal=USART1_TX
PB0.Signal=S_TIM3_CH3
PB1.Signal=S_TIM3_CH4
PB10.GPIOParameters=GPIO_Label
PB10.GPIO_Label=SCL_Boost
PB10.Signal=GPIO_Input
PB11.GPIOParameters=GPIO_Label
PB11.GPIO_Label=SDA_Boost
PB11.Signal=GPIO_Input
PB12.GPIOParameters=GPIO_Label
PB12.GPIO_Label=boostWkUp
PB12.Signal=GPIO_Output
PB13.GPIOParameters=GPIO_Label
PB13.GPIO_Label=powerOn
PB13.Signal=GPIO_Output
PB2.GPIOParameters=GPIO_Label
PB2.GPIO_Label=IRQ_Boost
PB2.Signal=GPIO_Input
PB3.Signal=S_TIM2_CH2
PB4.GPIOParameters=GPIO_Label
PB4.GPIO_Label=LED2
PB4.Signal=GPIO_Output
PB5.GPIOParameters=GPIO_Label
PB5.GPIO_Label=EN_5V
PB5.Signal=GPIO_Output
PB6.Signal=S_TIM4_CH1
PB7.Signal=S_TIM4_CH2
PB8.Signal=S_TIM4_CH3
PB9.Signal=S_TIM4_CH4
PC13-TAMPER-RTC.GPIOParameters=GPIO_Label
PC13-TAMPER-RTC.GPIO_Label=LED1
PC13-TAMPER-RTC.Signal=GPIO_Output
PC14-OSC32_IN.Signal=RCC_OSC32_IN
PC15-OSC32_OUT.Signal=RCC_OSC32_OUT
PD0-OSC_IN.Mode=HSE-External-Oscillator
PD0-OSC_IN.Signal=RCC_OSC_IN
PD1-OSC_OUT.Mode=HSE-External-Oscillator
PD1-OSC_OUT.Signal=RCC_OSC_OUT
RCC.SYSCLKFreq_VALUE=72000000
RCC.SYSCLKSource=RCC_SYSCLKSOURCE_PLLCLK
board=custom

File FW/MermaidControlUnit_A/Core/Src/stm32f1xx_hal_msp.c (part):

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
    __HAL_RCC_GPIOA_CLK_ENABLE();
    /**ADC1 GPIO Configuration
    PA4     ------> ADC1_IN4
    PA5     ------> ADC1_IN5
    */
    GPIO_InitStruct.Pin = GPIO_PIN_4|GPIO_PIN_5;
    GPIO_InitStruct.Mode = GPIO_MODE_ANALOG;
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    __HAL_RCC_ADC1_CLK_DISABLE();

    /**ADC1 GPIO Configuration
    PA4     ------> ADC1_IN4
    PA5     ------> ADC1_IN5
    */
    HAL_GPIO_DeInit(GPIOA, GPIO_PIN_4|GPIO_PIN_5);

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    __HAL_RCC_GPIOA_CLK_ENABLE();
    __HAL_RCC_GPIOB_CLK_ENABLE();
    /**TIM2 GPIO Configuration
    PA2     ------> TIM2_CH3
    PA3     ------> TIM2_CH4
    PA15     ------> TIM2_CH1
    PB3     ------> TIM2_CH2
    */
    GPIO_InitStruct.Pin = GPIO_PIN_2|GPIO_PIN_3|GPIO_PIN_15;
    GPIO_InitStruct.Mode = GPIO_MODE_AF_PP;
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    __HAL_RCC_GPIOA_CLK_ENABLE();
    __HAL_RCC_GPIOB_CLK_ENABLE();
    /**TIM3 GPIO Configuration
    PA6     ------> TIM3_CH1
    PA7     ------> TIM3_CH2
    PB0     ------> TIM3_CH3
    PB1     ------> TIM3_CH4
    */
    GPIO_InitStruct.Pin = GPIO_PIN_6|GPIO_PIN_7;
    GPIO_InitStruct.Mode = GPIO_MODE_AF_PP;
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
    __HAL_RCC_GPIOB_CLK_ENABLE();
    /**TIM4 GPIO Configuration
    PB6     ------> TIM4_CH1
    PB7     ------> TIM4_CH2
    PB8     ------> TIM4_CH3
    PB9     ------> TIM4_CH4
    */
    GPIO_InitStruct.Pin = GPIO_PIN_6|GPIO_PIN_7|GPIO_PIN_8|GPIO_PIN_9;
    GPIO_InitStruct.Mode = GPIO_MODE_AF_PP;
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
    __HAL_RCC_GPIOA_CLK_ENABLE();
    /**USART1 GPIO Configuration
    PA9     ------> USART1_TX
    PA10     ------> USART1_RX
    */
    GPIO_InitStruct.Pin = GPIO_PIN_9;
    GPIO_InitStruct.Mode = GPIO_MODE_AF_PP;
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    __HAL_RCC_USART1_CLK_DISABLE();

    /**USART1 GPIO Configuration
    PA9     ------> USART1_TX
    PA10     ------> USART1_RX
    */
    HAL_GPIO_DeInit(GPIOA, GPIO_PIN_9|GPIO_PIN_10);

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
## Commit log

2024-11-23 init IR working
2024-12-03 barebone neopiixel not working
2024-12-06 ws2812 lib try 2
2024-12-06 working neopixel lib
2024-12-07 prototype_V1
2024-12-23 Restructured repo
2024-12-23 hw project init
2024-12-26 folders reorganized, schematic progress
2024-12-26 pinmapping
2024-12-28 HW design progress
2024-12-29 hw progress
2025-01-17 production rev A
2025-01-19 prev fw migrated to project
2025-02-04 ibom added
2025-02-04 schematic added, folder structure updated
2025-03-01 init debug
2025-03-04 BQ NTC retuned
2025-03-08 longer string code added

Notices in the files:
FW/MermaidControlUnit_A/Core/Src/stm32f1xx_hal_msp.c:
Copyright (c) 2025 STMicroelectronics.
All rights reserved.
This software is licensed under terms that can be found in the LICENSE file
